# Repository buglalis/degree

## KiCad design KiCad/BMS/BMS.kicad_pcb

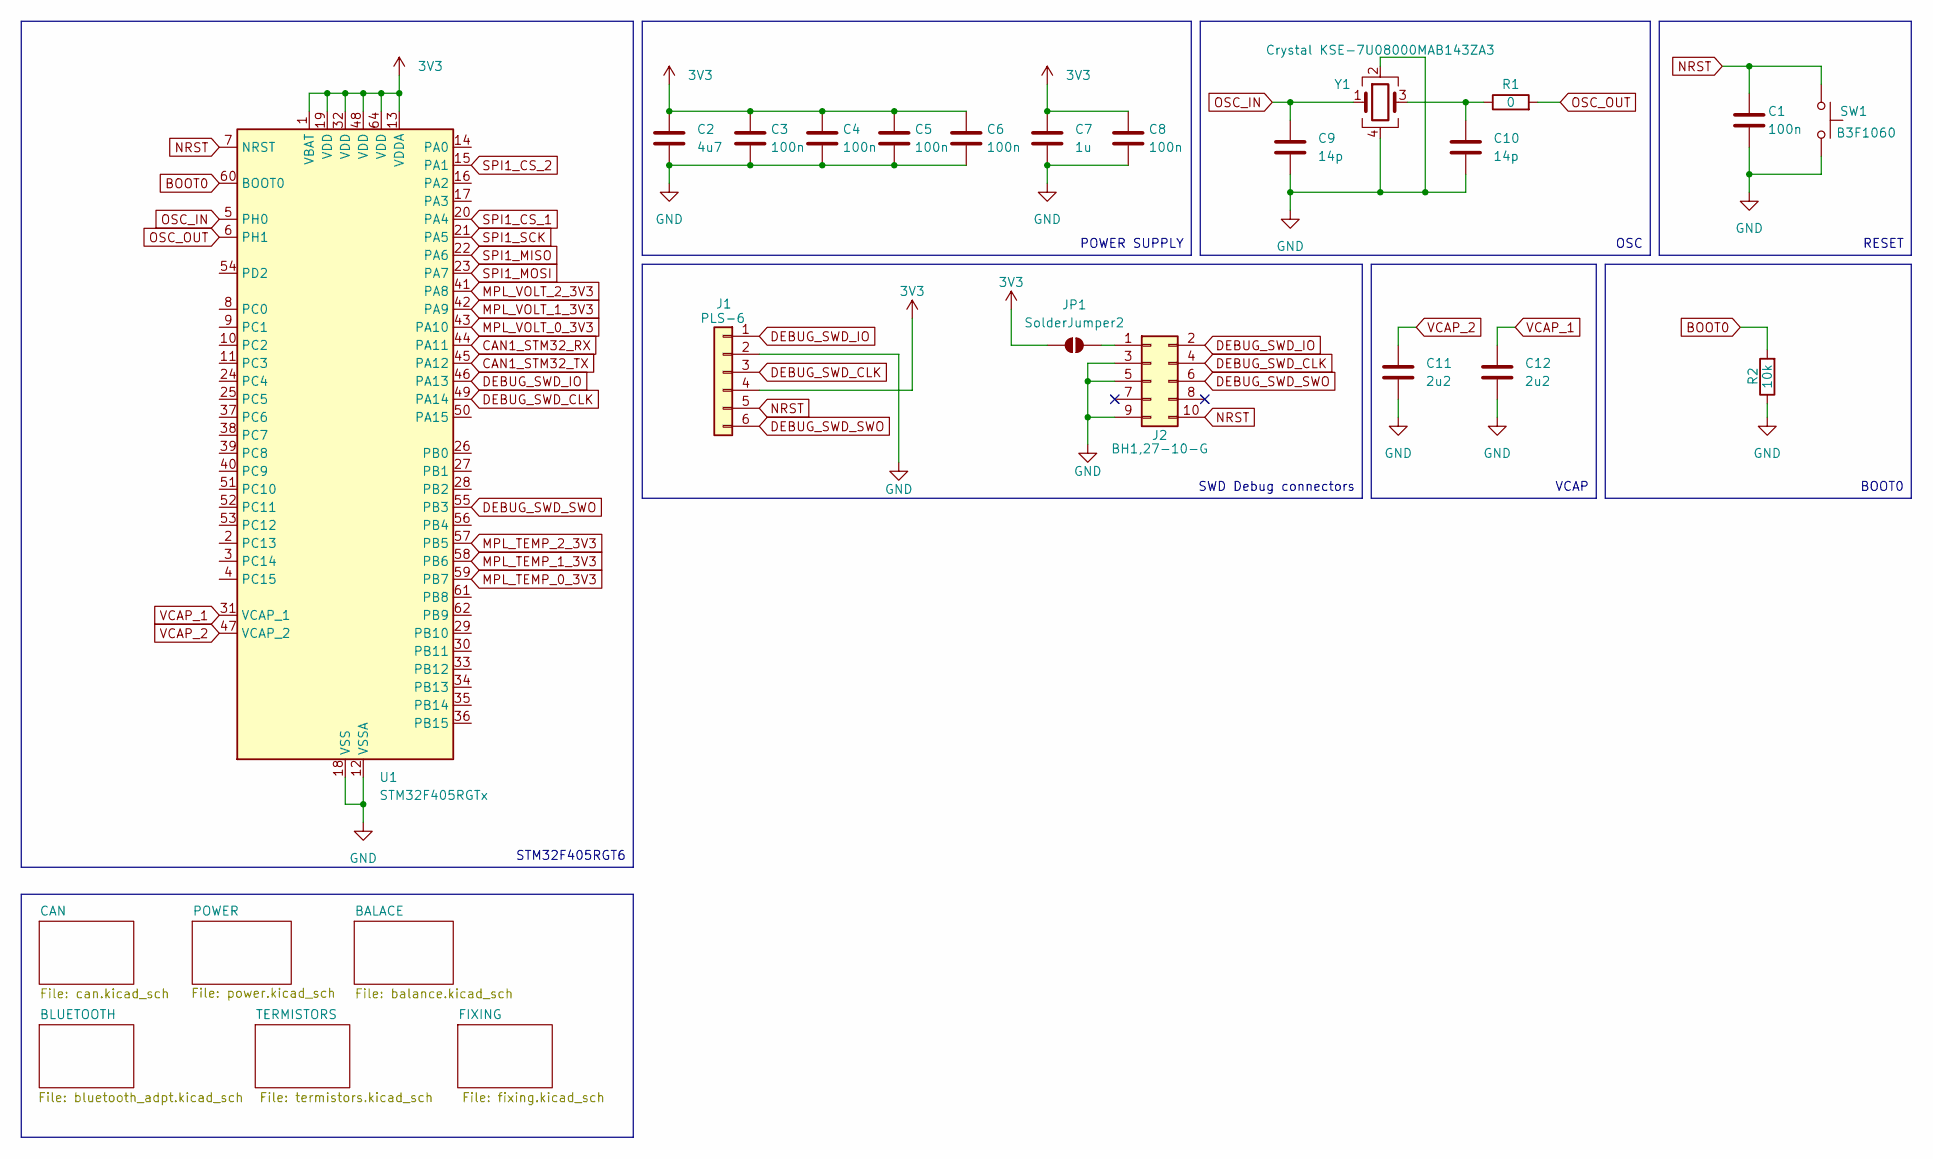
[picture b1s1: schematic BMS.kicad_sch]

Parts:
C1, C3, C4, C5, C6, C8: 100n; C_0603_1608Metric
C2: 4u7; C_0603_1608Metric
C7: 1u; C_0603_1608Metric
C9, C10: 14p; C_0603_1608Metric
C11, C12: 2u2; C_0603_1608Metric
J1: PLS-6; PinHeader_1x06_P2.54mm_Vertical
J2: BH1,27-10-G; PinHeader_2x05_P1.27mm_Vertical
JP1: SolderJumper2; SolderJumper-2_P1.3mm_Open_RoundedPad1.0x1.5mm
R1: 0; R_0603_1608Metric
R2: 10k; R_0603_1608Metric
SW1: B3F1060; SW_PUSH_6mm_H5mm
U1: STM32F405RGTx; LQFP-64_10x10mm_P0.5mm
Y1: Crystal KSE-7U08000MAB143ZA3; Crystal_SMD_SeikoEpson_TSX3225-4Pin_3.2x2.5mm

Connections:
3V3: C2.1, C3.1, C4.1, C5.1, C6.1, C7.1, C8.1, J1.4, JP1.1 (A), U1.1 (VBAT), U1.13 (VDDA), U1.19 (VDD), U1.32 (VDD), U1.48 (VDD), U1.64 (VDD); also elsewhere on the board
BOOT0: R2.2, U1.60 (BOOT0)
CAN1_STM32_RX: U1.44 (PA11); also elsewhere on the board
CAN1_STM32_TX: U1.45 (PA12); also elsewhere on the board
DEBUG_SWD_CLK: J1.3, J2.4, U1.49 (PA14)
DEBUG_SWD_IO: J1.1, J2.2, U1.46 (PA13)
DEBUG_SWD_SWO: J1.6, J2.6, U1.55 (PB3)
GND: C1.1, C2.2, C3.2, C4.2, C5.2, C6.2, C7.2, C8.2, C9.1, C10.2, C11.2, C12.2, J1.2, J2.3, J2.5, J2.9, R2.1, SW1.2, U1.12 (VSSA), U1.18 (VSS), U1.63 (VSS), Y1.2, Y1.4; also elsewhere on the board
MPL_TEMP_0_3V3: U1.59 (PB7); also elsewhere on the board
MPL_TEMP_1_3V3: U1.58 (PB6); also elsewhere on the board
MPL_TEMP_2_3V3: U1.57 (PB5); also elsewhere on the board
MPL_VOLT_0_3V3: U1.43 (PA10); also elsewhere on the board
MPL_VOLT_1_3V3: U1.42 (PA9); also elsewhere on the board
MPL_VOLT_2_3V3: U1.41 (PA8); also elsewhere on the board
NRST: C1.2, J1.5, J2.10, SW1.1, U1.7 (NRST)
unnamed: C10.1, R1.1, Y1.3
unnamed: J2.1, JP1.2 (B)
OSC_IN: C9.2, U1.5 (PH0), Y1.1
OSC_OUT: R1.2, U1.6 (PH1)
SPI1_CS_1: U1.20 (PA4); also elsewhere on the board
SPI1_CS_2: U1.15 (PA1); also elsewhere on the board
SPI1_MISO: U1.22 (PA6); also elsewhere on the board
SPI1_MOSI: U1.23 (PA7)
SPI1_SCK: U1.21 (PA5); also elsewhere on the board
VCAP_1: C12.1, U1.31 (VCAP_1)
VCAP_2: C11.1, U1.47 (VCAP_2)

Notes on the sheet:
RESET
SWD Debug connectors
OSC
POWER SUPPLY
VCAP
STM32F405RGT6
BOOT0

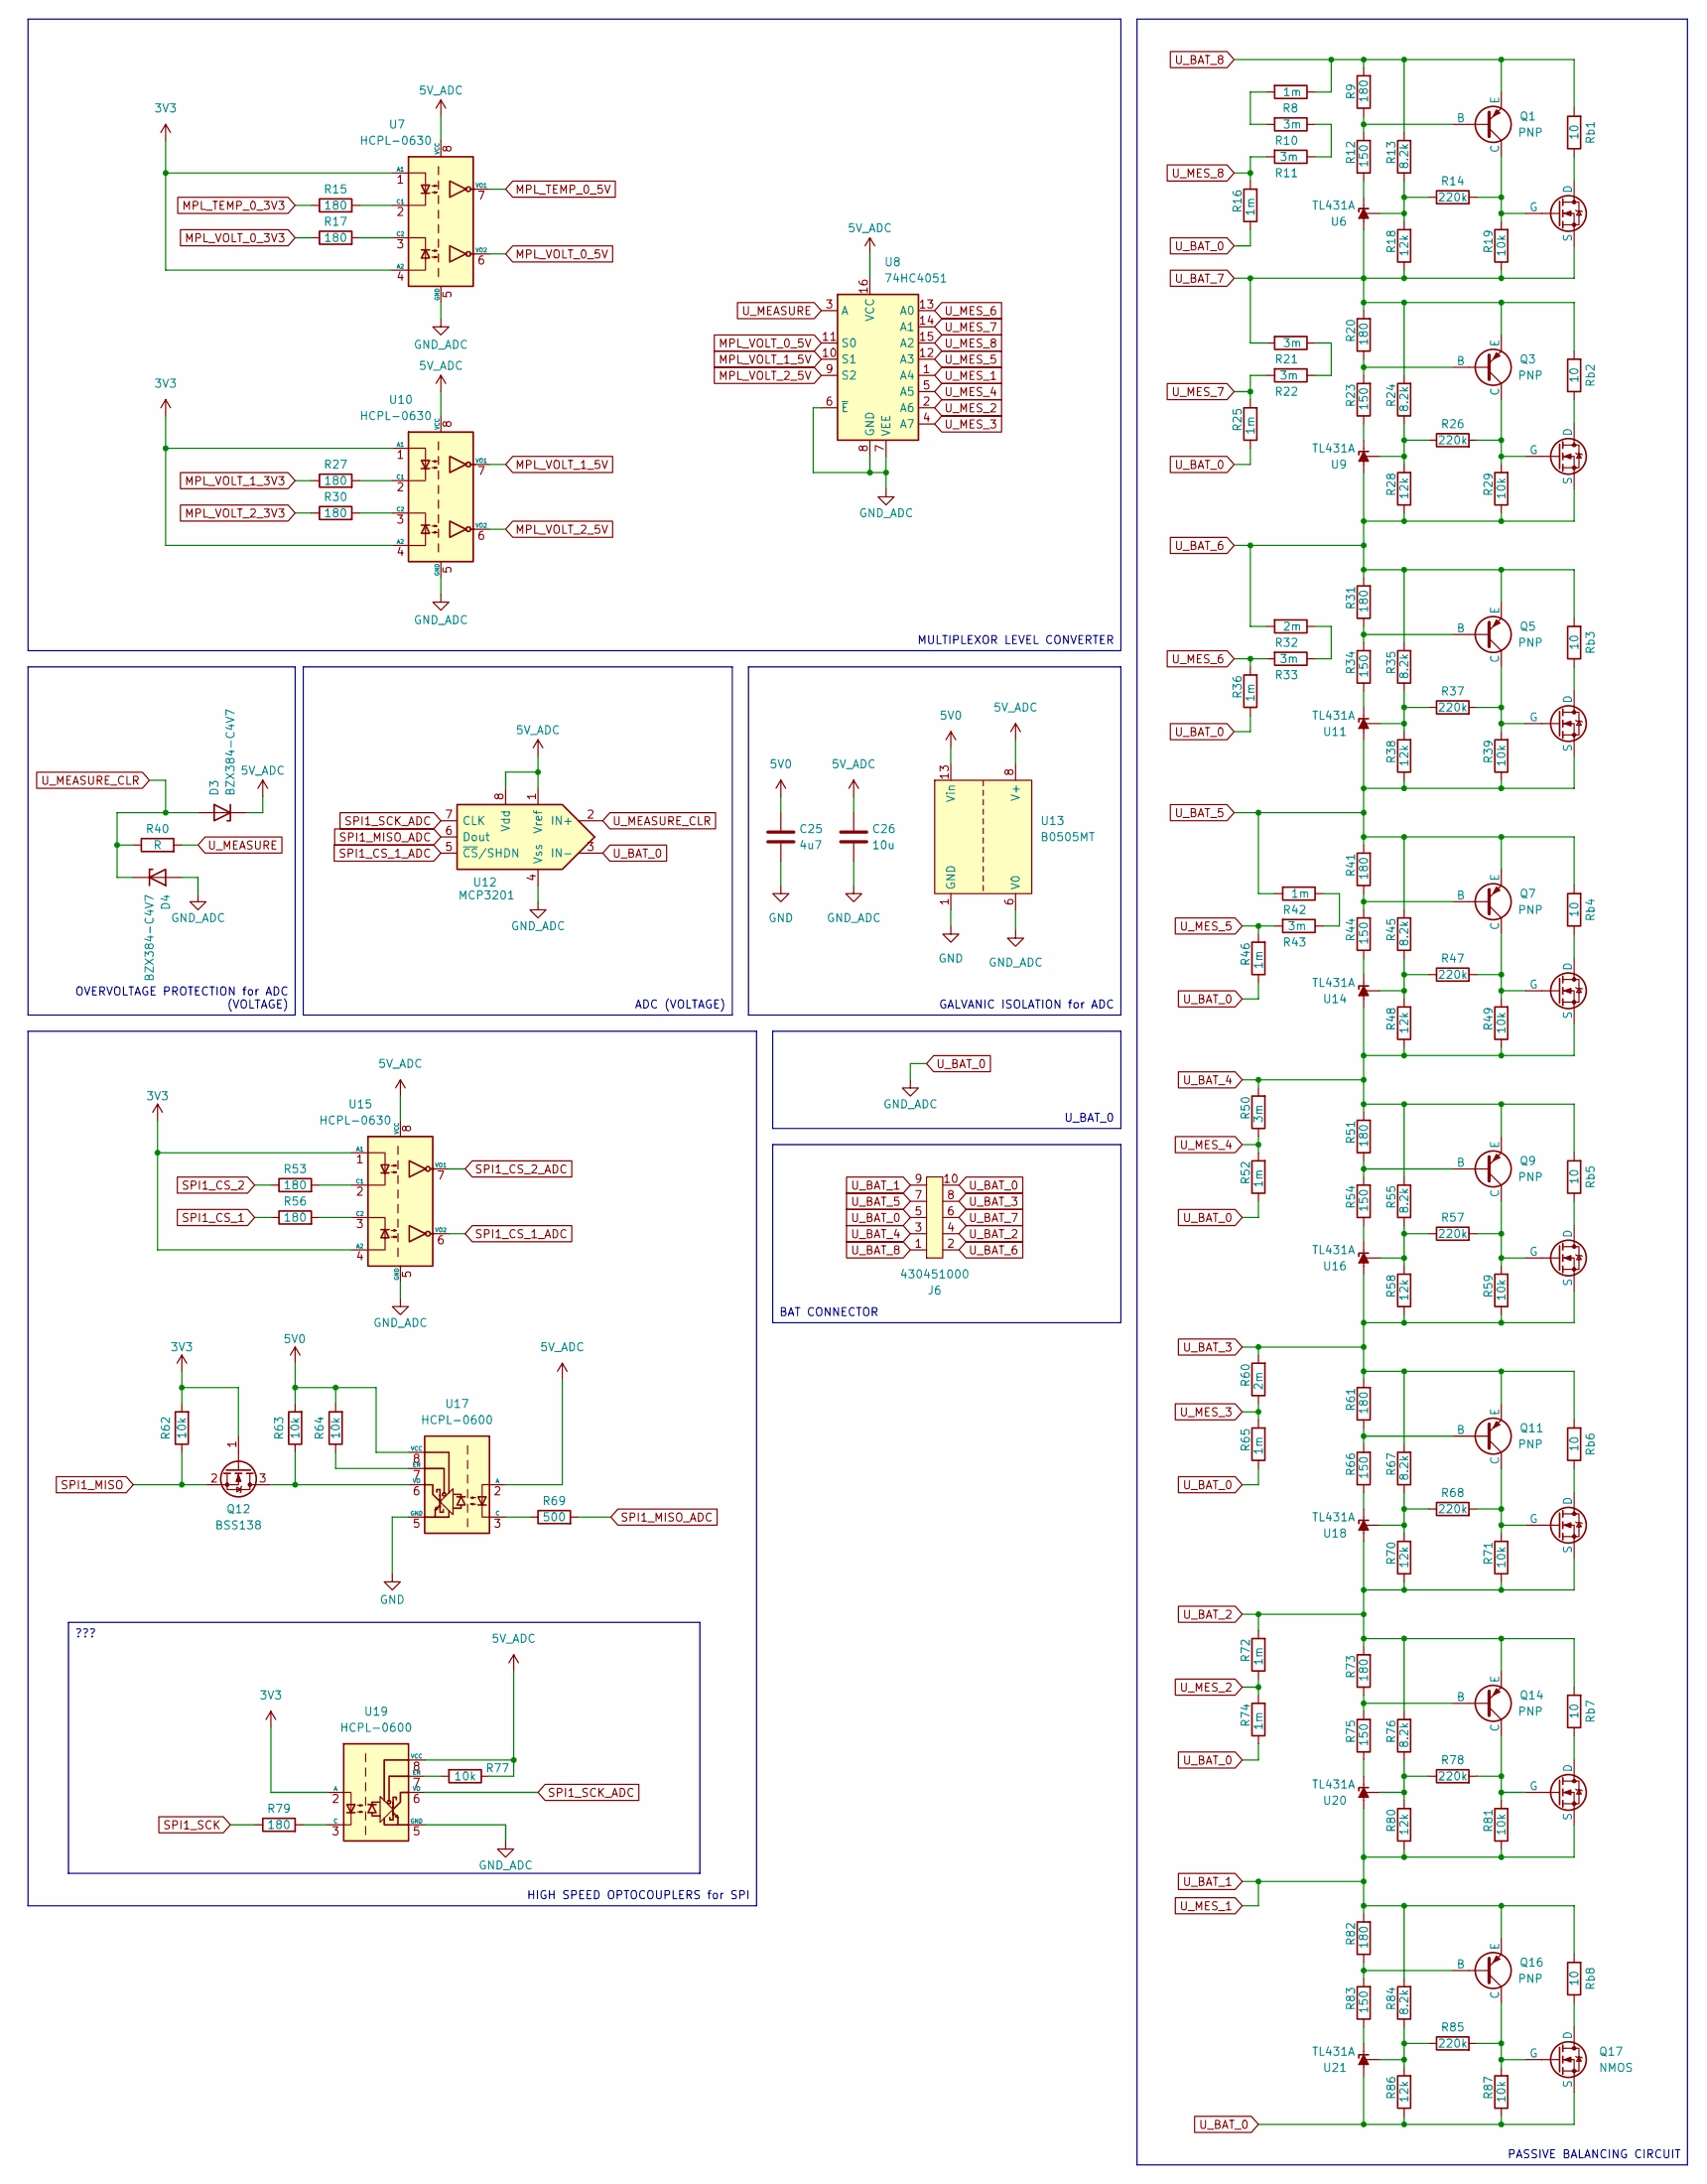
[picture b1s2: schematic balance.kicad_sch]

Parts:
C25: 4u7; C_0603_1608Metric
C26: 10u; C_0603_1608Metric
D3, D4: BZX384-C4V7; D_SOD-323_HandSoldering
J6: 430451000; Molex_Micro-Fit_3.0_43045-1000_2x05_P3.00mm_Horizontal
Q1, Q3, Q5, Q7, Q9, Q11, Q14, Q16: PNP; SOT-23-3
Q2, Q4, Q6, Q8, Q10, Q13, Q15, Q17: NMOS; TO-252-2
Q12: BSS138; SOT-23
R8, R16, R25, R36, R42, R46, R52, R65, R72, R74: 1m; R_0603_1608Metric
R9, R15, R17, R20, R27, R30, R31, R41, R51, R53, R56, R61, R73, R79, R82: 180; R_0603_1608Metric
R10, R11, R21, R22, R33, R43, R50: 3m; R_0603_1608Metric
R12, R23, R34, R44, R54, R66, R75, R83: 150; R_0603_1608Metric
R13, R24, R35, R45, R55, R67, R76, R84: 8.2k; R_0603_1608Metric
R14, R26, R37, R47, R57, R68, R78, R85: 220k; R_0603_1608Metric
R18, R28, R38, R48, R58, R70, R80, R86: 12k; R_0603_1608Metric
R19, R29, R39, R49, R59, R62, R63, R64, R71, R77, R81, R87: 10k; R_0603_1608Metric
R32, R60: 2m; R_0603_1608Metric
R40: R; R_0603_1608Metric
R69: 500; R_0603_1608Metric
Rb1, Rb2, Rb3, Rb4, Rb5, Rb6, Rb7, Rb8: 10; R_1206_3216Metric
U6, U9, U11, U14, U16, U18, U20, U21: TL431A; SOT-23
U7, U10, U15: HCPL-0630; SOIC-8_3.9x4.9mm_P1.27mm
U8: 74HC4051; TSSOP-16_4.4x5mm_P0.65mm
U12: MCP3201; SO-8_3.9x4.9mm_P1.27mm
U13: B0505MT
U17, U19: HCPL-0600; SOIC-8_3.9x4.9mm_P1.27mm

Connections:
3V3: Q12.1 (G), R62.2, U7.1 (A1), U7.4 (A2), U10.1 (A1), U10.4 (A2), U15.1 (A1), U15.4 (A2), U19.2 (A); also elsewhere on the board
5V0: C25.1, R63.2, R64.2, U13.13 (Vin), U13.14 (Vin), U17.8 (VCC); also elsewhere on the board
5V_ADC: C26.1, D3.1 (K), R77.1, U7.8 (VCC), U8.16 (VCC), U10.8 (VCC), U12.1 (Vref), U12.8 (Vdd), U13.8 (V+), U15.8 (VCC), U17.2 (A), U19.8 (VCC); also elsewhere on the board
GND: C25.2, U13.1 (GND), U13.2 (GND), U17.5 (GND); also elsewhere on the board
MPL_TEMP_0_3V3: R15.1; also elsewhere on the board
MPL_TEMP_0_5V: U7.7 (VO1); also elsewhere on the board
MPL_VOLT_0_3V3: R17.1; also elsewhere on the board
MPL_VOLT_0_5V: U7.6 (VO2), U8.11 (S0)
MPL_VOLT_1_3V3: R27.1; also elsewhere on the board
MPL_VOLT_1_5V: U8.10 (S1), U10.7 (VO1)
MPL_VOLT_2_3V3: R30.1; also elsewhere on the board
MPL_VOLT_2_5V: U8.9 (S2), U10.6 (VO2)
unnamed: Q1.2 (B), R9.1, R12.2
unnamed: Q1.1 (C), Q2.2 (G), R14.2, R19.2
unnamed: Q2.1 (D), Rb1.1
unnamed: Q3.2 (B), R20.1, R23.2
unnamed: Q3.1 (C), Q4.2 (G), R26.2, R29.2
unnamed: Q4.1 (D), Rb2.1
unnamed: Q5.2 (B), R31.1, R34.2
unnamed: Q5.1 (C), Q6.2 (G), R37.2, R39.2
unnamed: Q6.1 (D), Rb3.1
unnamed: Q7.2 (B), R41.1, R44.2
unnamed: Q7.1 (C), Q8.2 (G), R47.2, R49.2
unnamed: Q8.1 (D), Rb4.1
unnamed: Q9.2 (B), R51.1, R54.2
unnamed: Q10.1 (D), Rb5.1
unnamed: Q9.1 (C), Q10.2 (G), R57.2, R59.2
unnamed: Q11.2 (B), R61.1, R66.2
unnamed: Q11.1 (C), Q13.2 (G), R68.2, R71.2
unnamed: Q12.3 (D), R63.1, U17.6 (VO)
unnamed: Q13.1 (D), Rb6.1
unnamed: Q14.2 (B), R73.1, R75.2
unnamed: Q14.1 (C), Q15.2 (G), R78.2, R81.2
unnamed: Q15.1 (D), Rb7.1
unnamed: Q16.2 (B), R82.1, R83.2
unnamed: Q16.1 (C), Q17.2 (G), R85.2, R87.2
unnamed: Q17.1 (D), Rb8.1
unnamed: R10.1, R11.1
unnamed: R8.2, R10.2
unnamed: R21.1, R22.1
unnamed: R32.1, R33.1
unnamed: R42.1, R43.1
unnamed: R12.1, U6.2 (K)
unnamed: R13.1, R14.1, R18.2, U6.1 (REF)
unnamed: R15.2, U7.2 (C1)
unnamed: R17.2, U7.3 (C2)
unnamed: R23.1, U9.2 (K)
unnamed: R24.1, R26.1, R28.2, U9.1 (REF)
unnamed: R27.2, U10.2 (C1)
unnamed: R30.2, U10.3 (C2)
unnamed: R34.1, U11.2 (K)
unnamed: R35.1, R37.1, R38.2, U11.1 (REF)
unnamed: R44.1, U14.2 (K)
unnamed: R45.1, R47.1, R48.2, U14.1 (REF)
unnamed: R53.2, U15.2 (C1)
unnamed: R56.2, U15.3 (C2)
unnamed: R54.1, U16.2 (K)
unnamed: R55.1, R57.1, R58.2, U16.1 (REF)
unnamed: R69.1, U17.3 (C)
unnamed: R64.1, U17.7 (EN)
unnamed: R66.1, U18.2 (K)
unnamed: R67.1, R68.1, R70.2, U18.1 (REF)
unnamed: R79.2, U19.3 (C)
unnamed: R77.2, U19.7 (EN)
unnamed: R75.1, U20.2 (K)
unnamed: R76.1, R78.1, R80.2, U20.1 (REF)
unnamed: R83.1, U21.2 (K)
unnamed: R84.1, R85.1, R86.2, U21.1 (REF)
SPI1_CS_1: R56.1; also elsewhere on the board
SPI1_CS_1_ADC: U12.5 (~CS/SHDN), U15.6 (VO2)
SPI1_CS_2: R53.1; also elsewhere on the board
SPI1_CS_2_ADC: U15.7 (VO1); also elsewhere on the board
SPI1_MISO: Q12.2 (S), R62.1; also elsewhere on the board
SPI1_MISO_ADC: R69.2, U12.6 (Dout); also elsewhere on the board
SPI1_SCK: R79.1; also elsewhere on the board
SPI1_SCK_ADC: U12.7 (CLK), U19.6 (VO); also elsewhere on the board
U_BAT_0: C26.2, D4.2 (A), J6.5, J6.10, Q17.3 (S), R16.1, R25.1, R36.1, R46.1, R52.1, R65.1, R74.1, R86.1, R87.1, U7.5 (GND), U8.6 (~E), U8.7 (VEE), U8.8 (GND), U10.5 (GND), U12.3 (IN-), U12.4 (Vss), U13.6 (V0), U13.7 (V0), U15.5 (GND), U19.5 (GND), U21.3 (A); also elsewhere on the board
U_BAT_1: J6.9, Q15.3 (S), Q16.3 (E), R80.1, R81.1, R82.2, R84.2, Rb8.2, U8.1 (A4), U20.3 (A)
U_BAT_2: J6.4, Q13.3 (S), Q14.3 (E), R70.1, R71.1, R72.2, R73.2, R76.2, Rb7.2, U18.3 (A)
U_BAT_3: J6.8, Q10.3 (S), Q11.3 (E), R58.1, R59.1, R60.2, R61.2, R67.2, Rb6.2, U16.3 (A)
U_BAT_4: J6.3, Q8.3 (S), Q9.3 (E), R48.1, R49.1, R50.2, R51.2, R55.2, Rb5.2, U14.3 (A)
U_BAT_5: J6.7, Q6.3 (S), Q7.3 (E), R38.1, R39.1, R41.2, R42.2, R45.2, Rb4.2, U11.3 (A)
U_BAT_6: J6.2, Q4.3 (S), Q5.3 (E), R28.1, R29.1, R31.2, R32.2, R35.2, Rb3.2, U9.3 (A)
U_BAT_7: J6.6, Q2.3 (S), Q3.3 (E), R18.1, R19.1, R20.2, R21.2, R24.2, Rb2.2, U6.3 (A)
U_BAT_8: J6.1, Q1.3 (E), R8.1, R9.2, R13.2, Rb1.2
U_MEASURE: R40.2, U8.3 (A)
U_MEASURE_CLR: D3.2 (A), D4.1 (K), R40.1, U12.2 (IN+)
U_MES_2: R72.1, R74.2, U8.2 (A6)
U_MES_3: R60.1, R65.2, U8.4 (A7)
U_MES_4: R50.1, R52.2, U8.5 (A5)
U_MES_5: R43.2, R46.2, U8.12 (A3)
U_MES_6: R33.2, R36.2, U8.13 (A0)
U_MES_7: R22.2, R25.2, U8.14 (A1)
U_MES_8: R11.2, R16.2, U8.15 (A2)

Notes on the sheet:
???
MULTIPLEXOR LEVEL CONVERTER
U_BAT_0
PASSIVE BALANCING CIRCUIT
ADC (VOLTAGE)
HIGH SPEED OPTOCOUPLERS for SPI
GALVANIC ISOLATION for ADC
BAT CONNECTOR
OVERVOLTAGE PROTECTION for ADC (VOLTAGE)

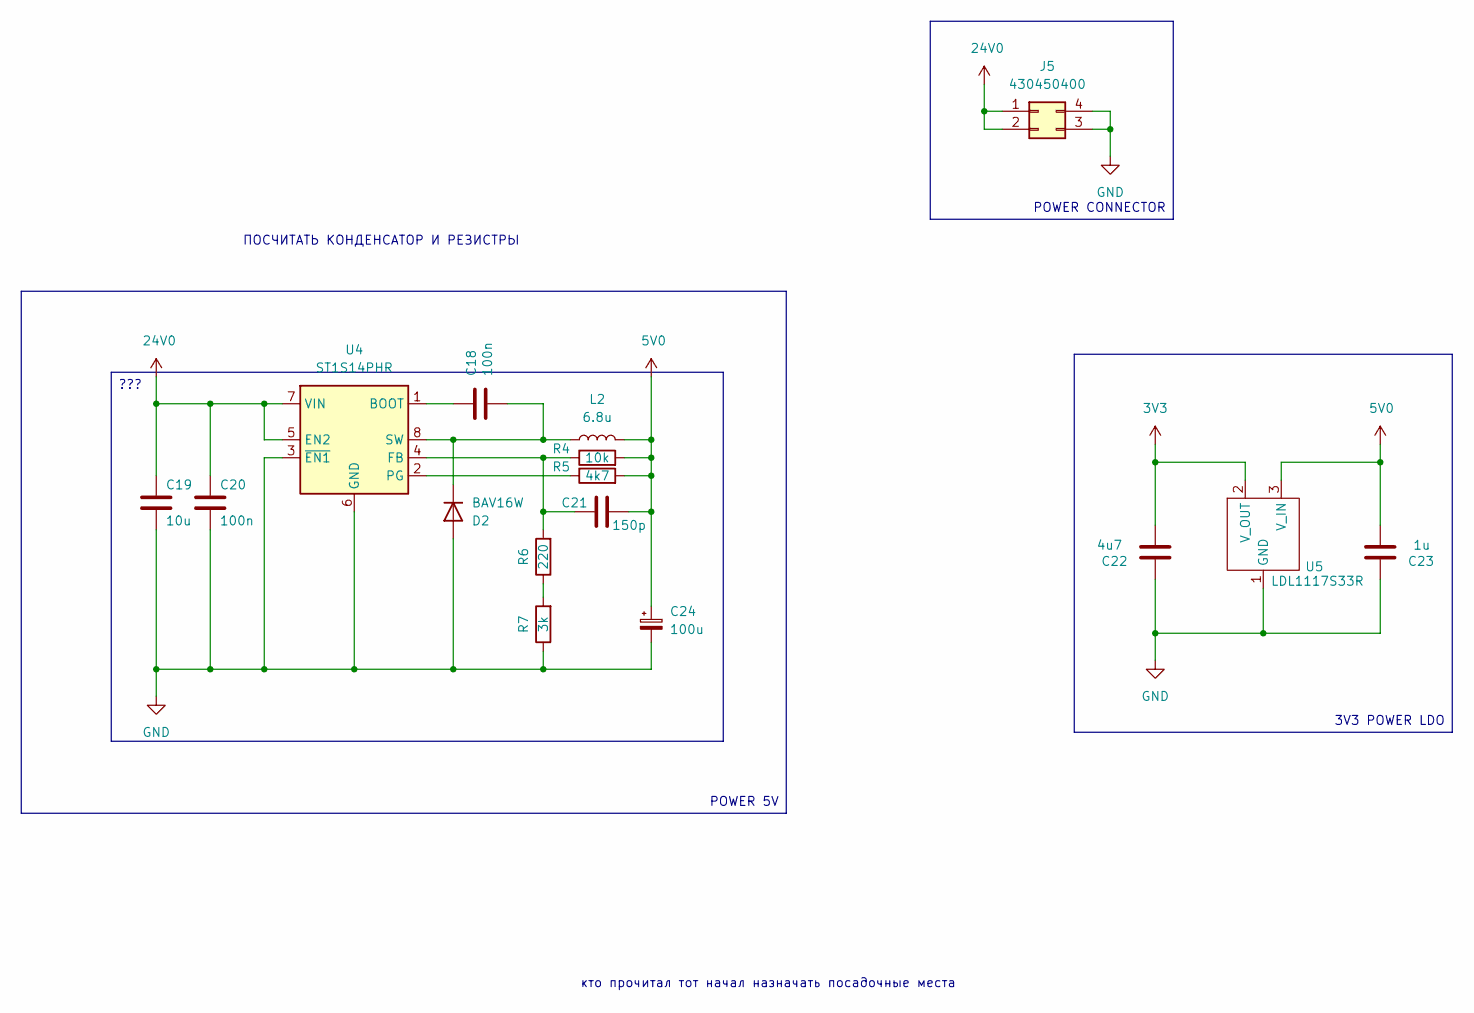
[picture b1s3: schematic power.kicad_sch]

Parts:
C18, C20: 100n; C_0603_1608Metric
C19: 10u; C_0603_1608Metric
C21: 150p; C_0603_1608Metric
C22: 4u7; C_0603_1608Metric
C23: 1u; C_0603_1608Metric
C24: 100u; CP_Radial_D6.3mm_P2.50mm
D2: BAV16W; D_SOD-123
J5: 430450400; Molex_Micro-Fit_3.0_43045-0400_2x02_P3.00mm_Horizontal
L2: 6.8u; CDCSAB0420-6R8M
R4: 10k; R_0603_1608Metric
R5: 4k7; R_0603_1608Metric
R6: 220; R_0603_1608Metric
R7: 3k; R_0603_1608Metric
U4: ST1S14PHR; TI_SO-PowerPAD-8
U5: LDL1117S33R; SOT-223-3_TabPin2

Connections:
3V3: C22.2, U5.2 (V_OUT); also elsewhere on the board
5V0: C21.2, C23.2, C24.1, L2.2, R4.2, R5.2, U5.3 (V_IN); also elsewhere on the board
24V0: C19.1, C20.1, J5.1, J5.2, U4.5 (EN2), U4.7 (VIN)
GND: C19.2, C20.2, C22.1, C23.1, C24.2, D2.2 (A), J5.3, J5.4, R7.1, U4.3 (~EN1), U4.6 (GND), U4.9 (PADGND), U5.1 (GND); also elsewhere on the board
unnamed: C18.2, D2.1 (K), L2.1, U4.8 (SW)
unnamed: R6.1, R7.2
unnamed: C18.1, U4.1 (BOOT)
unnamed: C21.1, R4.1, R6.2, U4.4 (FB)
unnamed: R5.1, U4.2 (PG)

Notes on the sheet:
кто прочитал тот начал назначать посадочные места
ПОСЧИТАТЬ КОНДЕНСАТОР И РЕЗИСТРЫ
POWER 5V
POWER CONNECTOR
3V3 POWER LDO
???

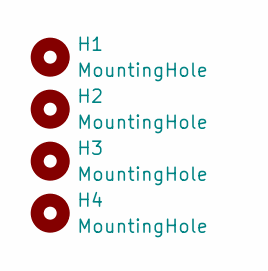
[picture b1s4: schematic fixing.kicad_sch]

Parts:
H1, H2, H3, H4: MountingHole; MountingHole_3.2mm_M3_Pad_Via

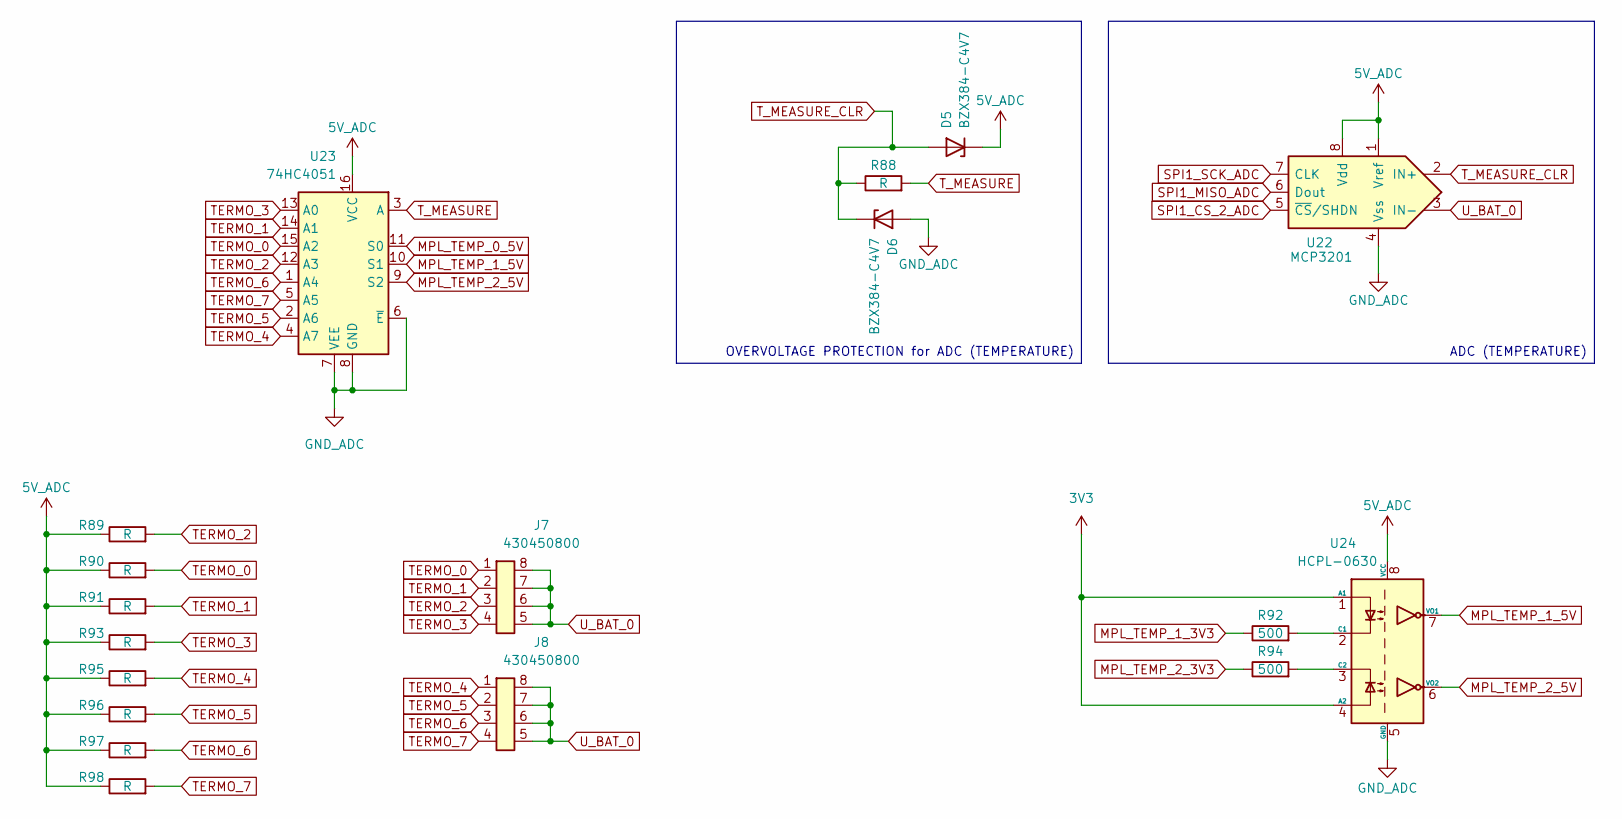
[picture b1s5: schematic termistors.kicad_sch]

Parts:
D5, D6: BZX384-C4V7; D_SOD-323_HandSoldering
J7, J8: 430450800; Molex_Micro-Fit_3.0_43045-0800_2x04_P3.00mm_Horizontal
R88, R89, R90, R91, R93, R95, R96, R97, R98: R; R_0603_1608Metric
R92, R94: 500; R_0603_1608Metric
U22: MCP3201; SO-8_3.9x4.9mm_P1.27mm
U23: 74HC4051; TSSOP-16_4.4x5mm_P0.65mm
U24: HCPL-0630; SOIC-8_3.9x4.9mm_P1.27mm

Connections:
3V3: U24.1 (A1), U24.4 (A2); also elsewhere on the board
5V_ADC: D5.1 (K), R89.1, R90.1, R91.1, R93.1, R95.1, R96.1, R97.1, R98.1, U22.1 (Vref), U22.8 (Vdd), U23.16 (VCC), U24.8 (VCC); also elsewhere on the board
MPL_TEMP_0_5V: U23.11 (S0); also elsewhere on the board
MPL_TEMP_1_3V3: R92.1; also elsewhere on the board
MPL_TEMP_1_5V: U23.10 (S1), U24.7 (VO1)
MPL_TEMP_2_3V3: R94.1; also elsewhere on the board
MPL_TEMP_2_5V: U23.9 (S2), U24.6 (VO2)
unnamed: R92.2, U24.2 (C1)
unnamed: R94.2, U24.3 (C2)
SPI1_CS_2_ADC: U22.5 (~CS/SHDN); also elsewhere on the board
SPI1_MISO_ADC: U22.6 (Dout); also elsewhere on the board
SPI1_SCK_ADC: U22.7 (CLK); also elsewhere on the board
TERMO_0: J7.1, R90.2, U23.15 (A2)
TERMO_1: J7.2, R91.2, U23.14 (A1)
TERMO_2: J7.3, R89.2, U23.12 (A3)
TERMO_3: J7.4, R93.2, U23.13 (A0)
TERMO_4: J8.1, R95.2, U23.4 (A7)
TERMO_5: J8.2, R96.2, U23.2 (A6)
TERMO_6: J8.3, R97.2, U23.1 (A4)
TERMO_7: J8.4, R98.2, U23.5 (A5)
T_MEASURE: R88.2, U23.3 (A)
T_MEASURE_CLR: D5.2 (A), D6.1 (K), R88.1, U22.2 (IN+)
U_BAT_0: D6.2 (A), J7.5, J7.6, J7.7, J7.8, J8.5, J8.6, J8.7, J8.8, U22.3 (IN-), U22.4 (Vss), U23.6 (~E), U23.7 (VEE), U23.8 (GND), U24.5 (GND); also elsewhere on the board

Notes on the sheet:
OVERVOLTAGE PROTECTION for ADC (TEMPERATURE)
ADC (TEMPERATURE)

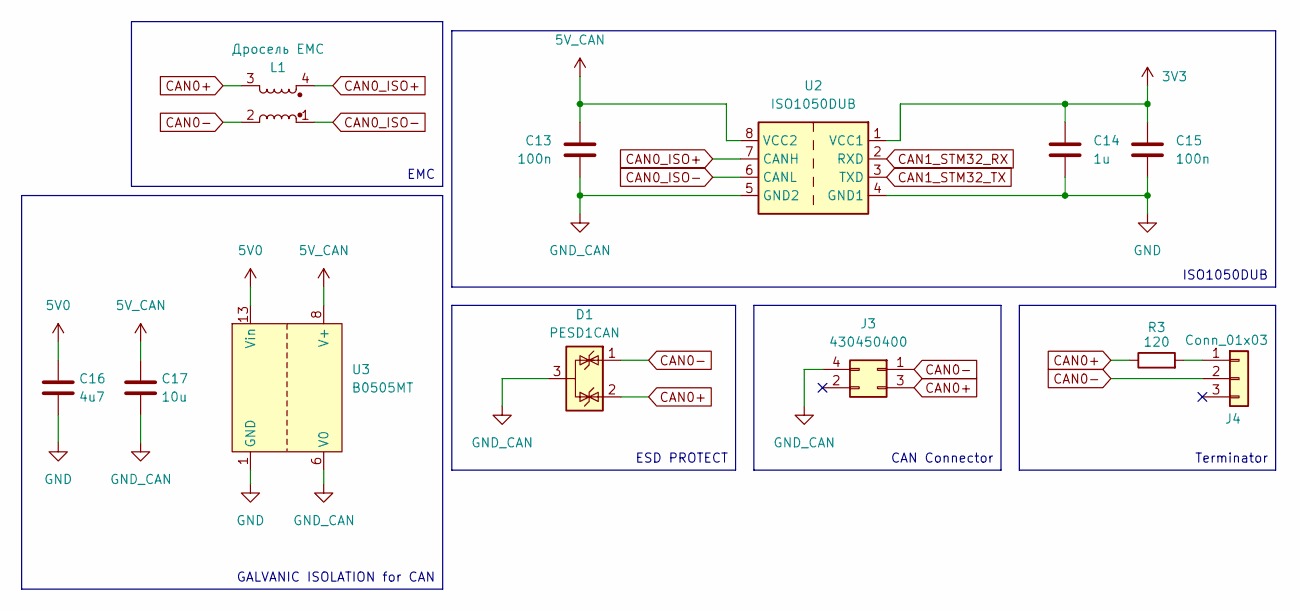
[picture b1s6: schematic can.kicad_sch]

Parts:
C13, C15: 100n; C_0603_1608Metric
C14: 1u; C_0603_1608Metric
C16: 4u7; C_0603_1608Metric
C17: 10u; C_0603_1608Metric
D1: PESD1CAN; SOT-23-3
J3: 430450400; Molex_Micro-Fit_3.0_43045-0400_2x02_P3.00mm_Horizontal
J4: Conn_01x03; PinHeader_1x03_P2.54mm_Vertical
L1: Дросель EMC; B82790C0513N201
R3: 120; R_0603_1608Metric
U2: ISO1050DUB; SOP-8_6.62x9.15mm_P2.54mm
U3: B0505MT

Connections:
3V3: C14.1, C15.1, U2.1 (VCC1); also elsewhere on the board
5V0: C16.1, U3.13 (Vin), U3.14 (Vin); also elsewhere on the board
5V_CAN: C13.1, C17.1, U2.8 (VCC2), U3.8 (V+)
CAN0+: D1.2 (K), J3.3, L1.3, R3.1
CAN0-: D1.1 (K), J3.1, J4.2, L1.2
CAN0_ISO+: L1.4, U2.7 (CANH)
CAN0_ISO-: L1.1, U2.6 (CANL)
CAN1_STM32_RX: U2.2 (RXD); also elsewhere on the board
CAN1_STM32_TX: U2.3 (TXD); also elsewhere on the board
GND: C14.2, C15.2, C16.2, U2.4 (GND1), U3.1 (GND), U3.2 (GND); also elsewhere on the board
GND_CAN: C13.2, C17.2, D1.3 (A), J3.4, U2.5 (GND2), U3.6 (V0), U3.7 (V0)
unnamed: J4.1, R3.2

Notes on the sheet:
Terminator
GALVANIC ISOLATION for CAN
EMC
CAN Connector
ESD PROTECT
ISO1050DUB

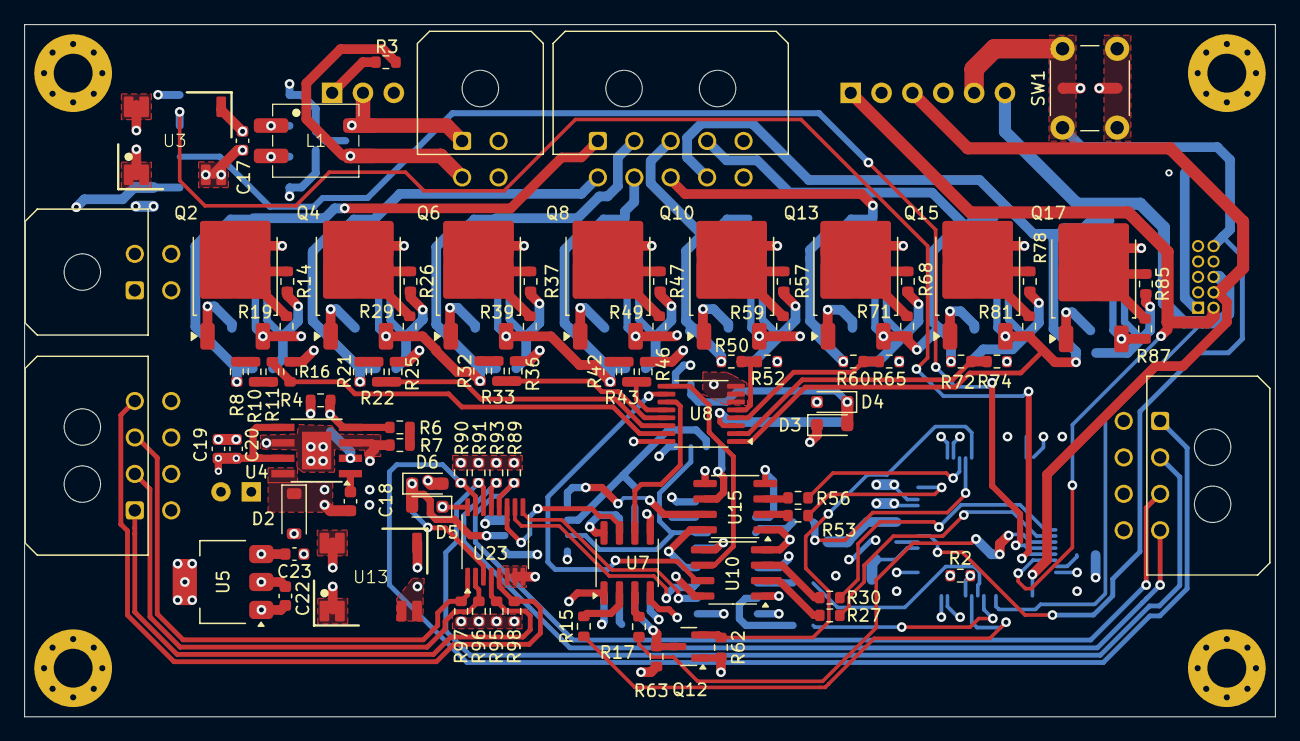
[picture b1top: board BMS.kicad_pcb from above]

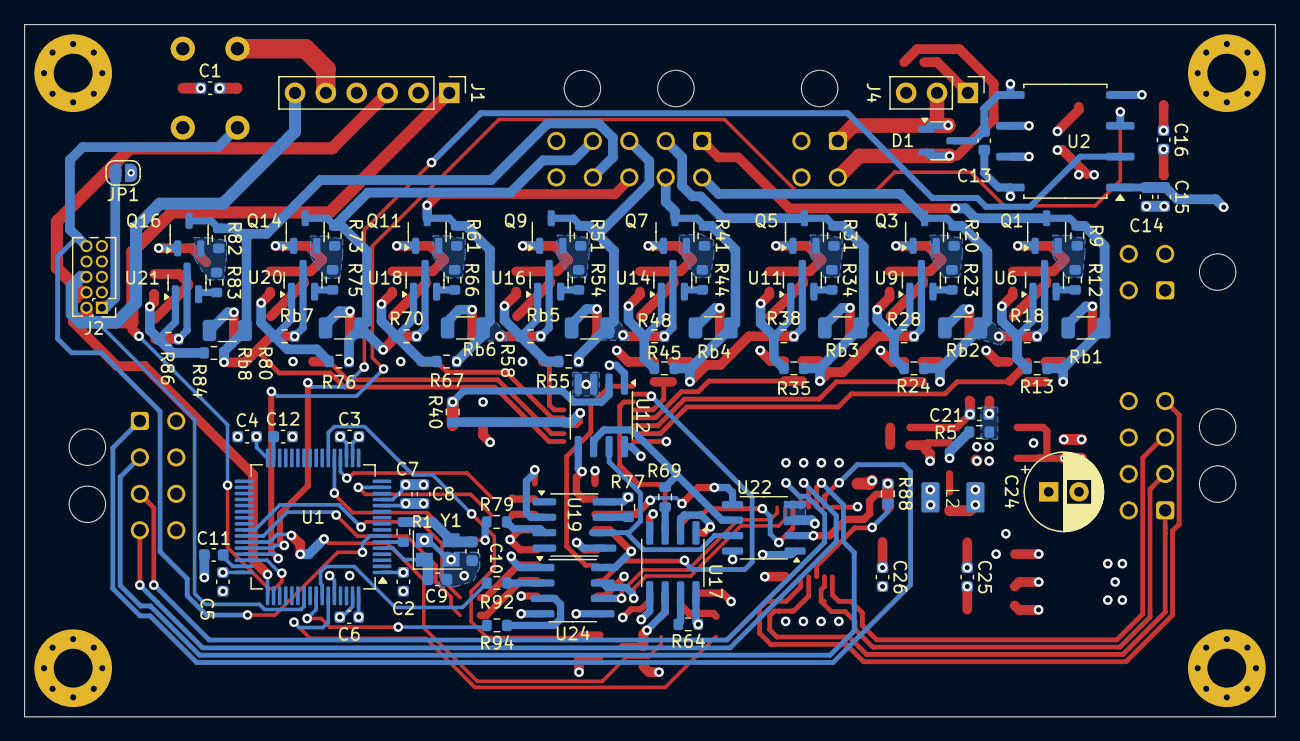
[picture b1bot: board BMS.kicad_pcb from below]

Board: 4 copper layers, 103.0 x 57.0 mm, 196 parts (100 on the bottom side), 136 nets.

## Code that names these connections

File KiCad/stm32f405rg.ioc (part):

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Mcu.Name=STM32F405RGTx
Mcu.Package=LQFP64
Mcu.UserName=STM32F405RGTx
PA1.GPIOParameters=GPIO_Label
PA1.GPIO_Label=SPI1_CS_2
PA1.Signal=GPIO_Output
PA10.GPIOParameters=GPIO_Label
PA10.GPIO_Label=OUT_M00
PA10.Signal=GPIO_Output
PA11.Mode=CAN_Activate
PA11.Signal=CAN1_RX
PA12.Mode=CAN_Activate
PA12.Signal=CAN1_TX
PA13.Mode=Trace_Asynchronous_SW
PA13.Signal=SYS_JTMS-SWDIO
PA14.Mode=Trace_Asynchronous_SW
PA14.Signal=SYS_JTCK-SWCLK
PA4.GPIOParameters=GPIO_Label
PA4.GPIO_Label=SPI1_CS1
PA4.Signal=GPIO_Output
PA5.Mode=RX_Only_Simplex_Unidirect_Master
PA5.Signal=SPI1_SCK
PA6.Mode=RX_Only_Simplex_Unidirect_Master
PA6.Signal=SPI1_MISO
PA7.Signal=SPI1_MOSI
PA8.GPIOParameters=GPIO_Label
PA8.GPIO_Label=OUT_M02
PA8.Signal=GPIO_Output
PA9.GPIOParameters=GPIO_Label
PA9.GPIO_Label=OUT_M01
PA9.Signal=GPIO_Output
PB3.Mode=Trace_Asynchronous_SW
PB3.Signal=SYS_JTDO-SWO
PB5.GPIOParameters=GPIO_Label
PB5.GPIO_Label=MPL_TEMP_2_3V3
PB5.Signal=GPIO_Output
PB6.GPIOParameters=GPIO_Label
PB6.GPIO_Label=MPL_TEMP_1_3V3
PB6.Signal=GPIO_Output
PB7.GPIOParameters=GPIO_Label
PB7.GPIO_Label=MPL_TEMP_0_3V3
PB7.Signal=GPIO_Output
PC7.GPIOParameters=GPIO_Label
PC7.GPIO_Label=OUT_M12
PC7.Signal=GPIO_Output
PC8.GPIOParameters=GPIO_Label
PC8.GPIO_Label=OUT_M11
PC8.Signal=GPIO_Output
PC9.GPIOParameters=GPIO_Label
PC9.GPIO_Label=OUT_M10
PC9.Signal=GPIO_Output
PH0-OSC_IN.Mode=HSE-External-Oscillator
PH0-OSC_IN.Signal=RCC_OSC_IN
PH1-OSC_OUT.Mode=HSE-External-Oscillator
PH1-OSC_OUT.Signal=RCC_OSC_OUT
RCC.HSE_VALUE=8000000
RCC.SYSCLKFreq_VALUE=168000000
RCC.SYSCLKSource=RCC_SYSCLKSOURCE_PLLCLK
board=custom

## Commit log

2025-03-13 12_03_2025 update
2025-03-15 14.03.2025
2025-03-19 18.03.2025
2025-03-21 22.03.2025
2025-03-23 23.03.2025
2025-03-25 25.03.2025
2025-03-28 27.03.2025
2025-03-30 30.03.2025
2025-04-04 rough routing is complete (04.04.2025)
2025-04-08 08.04.2025
2025-04-09 09.04.2025
2025-04-10 10.04.2025
2025-04-10 10.04.2025 presentation
2025-04-16 pupupu
2025-04-19 18.04.2025_final
2025-04-19 19.04.2025
2025-04-20 20.04.2025_true
2025-04-21 21.04.2025_beta
2025-04-23 23.04.2025
2025-04-28 27.04.2025
2025-05-21 fix hcpl 21.05.2025
2025-05-22 22.05.2025
2025-06-04 04.06.2025
